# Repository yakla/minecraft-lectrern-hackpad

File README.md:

# Minecraft Lectern Hackpad
A custom 6-key mechanical macro pad inspired by the Minecraft Lectern, designed for the **Hack Club Blueprint**.

## The Vision
the idea was i fast hackpad project with cool visuals. so i made it with a minecraft lectern block.
## Technical Specs
* **Controller:** Seeed Studio XIAO RP2040
* **Keys:** 6 Mechanical Switches (3x2 Matrix)
* **Visuals:** 128x32 OLED Display + WS2812B RGB LEDs
* **Firmware:** KMK / CircuitPython

# Hardware
* **XIAO RP2040** – The microController
* **6 x Mechanical Switches** - hackpad keys
* **1 x 0.91" White OLED** – Crisp 128x32 display for real-time status and custom graphics.
* **4 x WS2812B RGB LEDs** – Integrated lighting for that essential setup flex.
* **Custom 2-Layer PCB** – Engineered in KiCad 
* **6 x 1N4148W Diodes**

## Design Process
- **CAD:** Designed in **Onshape**. https://cad.onshape.com/documents/4aa1c7f92bdb34f3150a863a/w/03df906dbdf565c718d04fe4/e/68b5d359d9c8e5f142904c5d?renderMode=0&uiState=69c481ee307fe18aded3200f
- **PCB:** Custom 2-layer board designed in **KiCad** with SMD diode protection.            |

## cad

## pcb design

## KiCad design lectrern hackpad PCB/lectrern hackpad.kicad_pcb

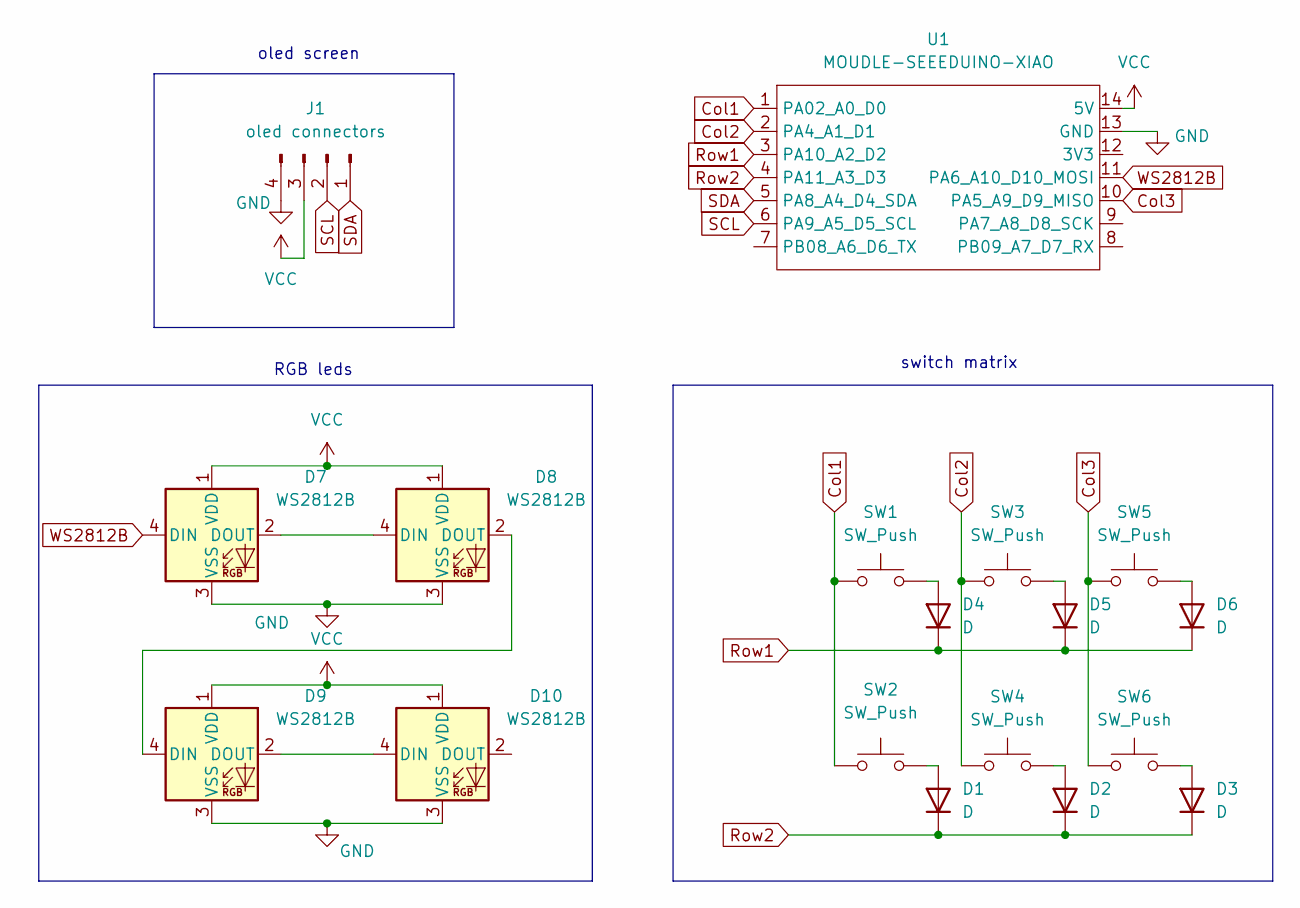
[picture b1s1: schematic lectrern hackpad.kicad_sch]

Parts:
D1, D2, D3, D4, D5, D6: D; D_5KPW_P7.62mm_Vertical_KathodeUp
D7, D8, D9, D10: WS2812B; LED_WS2812B_PLCC4_5.0x5.0mm_P3.2mm
J1: oled connectors; PinHeader_1x04_P2.54mm_Vertical
SW1, SW2, SW3, SW4, SW5, SW6: SW_Push; MX-Solderable-1U
U1: MOUDLE-SEEEDUINO-XIAO; XIAO-Generic-Hybrid-14P-2.54-21X17.8MM

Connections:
Col1: SW1.1, SW2.1, U1.1 (PA02_A0_D0)
Col2: SW3.1, SW4.1, U1.2 (PA4_A1_D1)
Col3: SW5.1, SW6.1, U1.10 (PA5_A9_D9_MISO)
GND: D7.3 (VSS), D8.3 (VSS), D9.3 (VSS), D10.3 (VSS), J1.4, U1.13 (GND)
unnamed: D1.2 (A), SW2.2
unnamed: D2.2 (A), SW4.2
unnamed: D3.2 (A), SW6.2
unnamed: D4.2 (A), SW1.2
unnamed: D5.2 (A), SW3.2
unnamed: D6.2 (A), SW5.2
unnamed: D7.2 (DOUT), D8.4 (DIN)
unnamed: D8.2 (DOUT), D9.4 (DIN)
unnamed: D9.2 (DOUT), D10.4 (DIN)
Row1: D4.1 (K), D5.1 (K), D6.1 (K), U1.3 (PA10_A2_D2)
Row2: D1.1 (K), D2.1 (K), D3.1 (K), U1.4 (PA11_A3_D3)
SCL: J1.2, U1.6 (PA9_A5_D5_SCL)
SDA: J1.1, U1.5 (PA8_A4_D4_SDA)
VCC: D7.1 (VDD), D8.1 (VDD), D9.1 (VDD), D10.1 (VDD), J1.3, U1.14 (5V)
WS2812B: D7.4 (DIN), U1.11 (PA6_A10_D10_MOSI)

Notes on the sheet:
RGB leds
switch matrix
oled screen

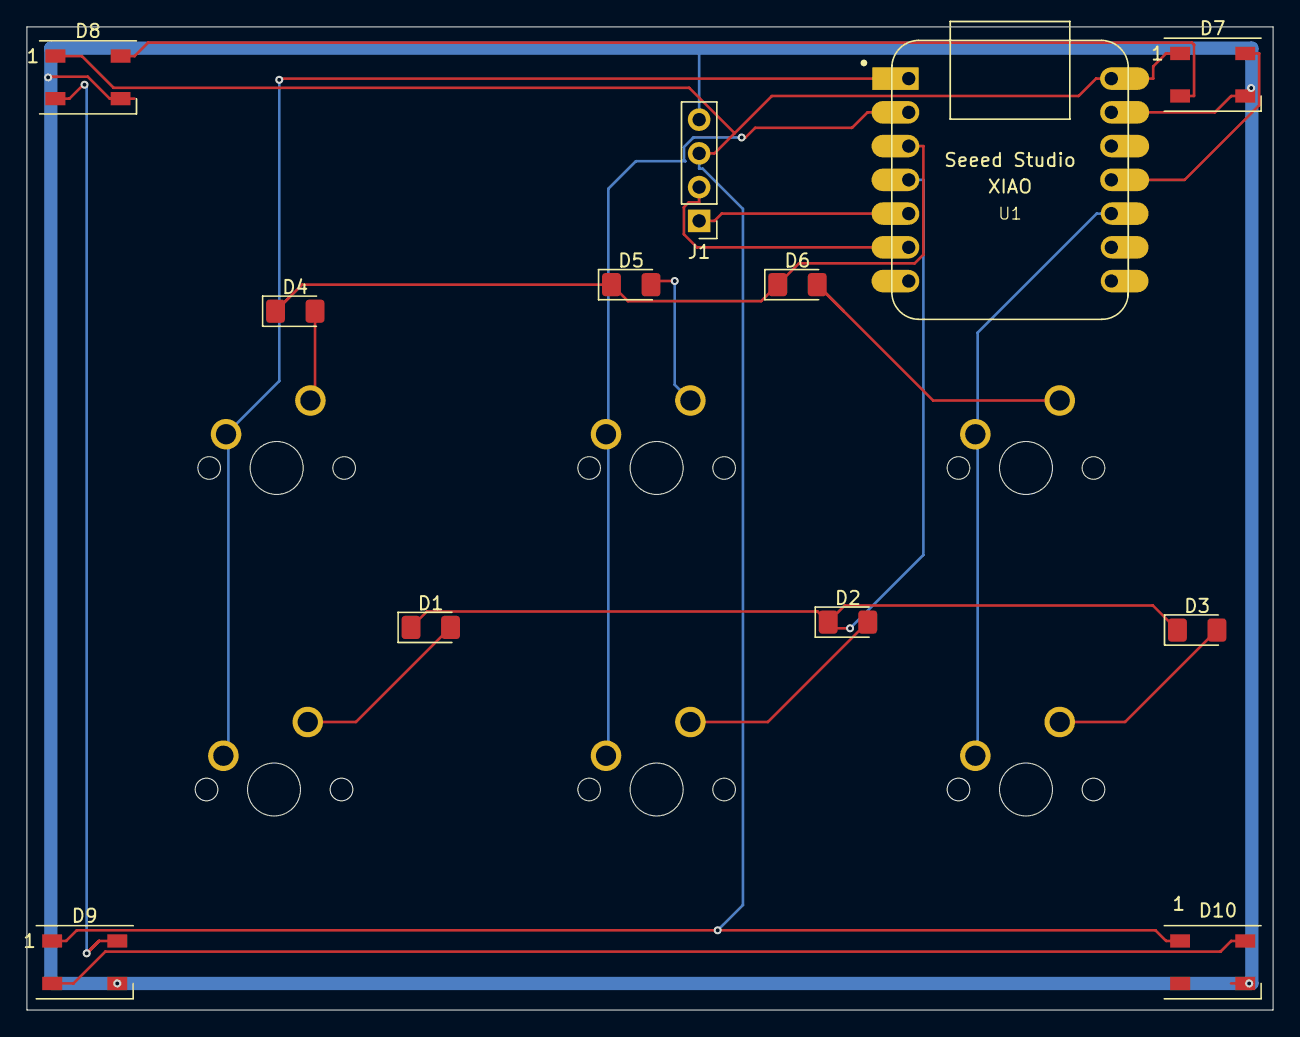
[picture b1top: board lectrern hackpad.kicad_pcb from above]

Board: 2 copper layers, 93.8 x 74.0 mm, 18 parts (0 on the bottom side), 19 nets.

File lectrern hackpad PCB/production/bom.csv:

Designator,Footprint,Quantity,Value,LCSC Part #
"D1, D2, D3, D4, D5, D6",1206,6,D,
"D10, D7, D8, D9",LED_WS2812B_PLCC4_5.0x5.0mm_P3.2mm,4,WS2812B,
J1,PinHeader_1x04_P2.54mm_Vertical,1,oled connectors,
"SW1, SW2, SW3, SW4, SW5, SW6",MX-Solderable-1U,6,SW_Push,
U1,XIAO-Generic-Hybrid-14P-2.54-21X17.8MM,1,MOUDLE-SEEEDUINO-XIAO,

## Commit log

2026-03-25 Initial commit: PCB design and Onshape model
2026-03-25 Add Bill of Materials section to README
2026-03-25 Replace xiao esp c3 with xiao rp2040 in README
2026-03-25 finish all the code firmware
2026-03-26 Update README with hardware details and BOM removal
    Added hardware specifications and removed BOM section.
2026-03-26 Add STEP file for panel design
2026-03-26 Update cad
2026-03-28 add the dxf laser files from the cad. still haven't added the minecraft texture to it
